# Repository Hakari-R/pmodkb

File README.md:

# pmodkb

---

4x4 MX Keyboard Pmod module

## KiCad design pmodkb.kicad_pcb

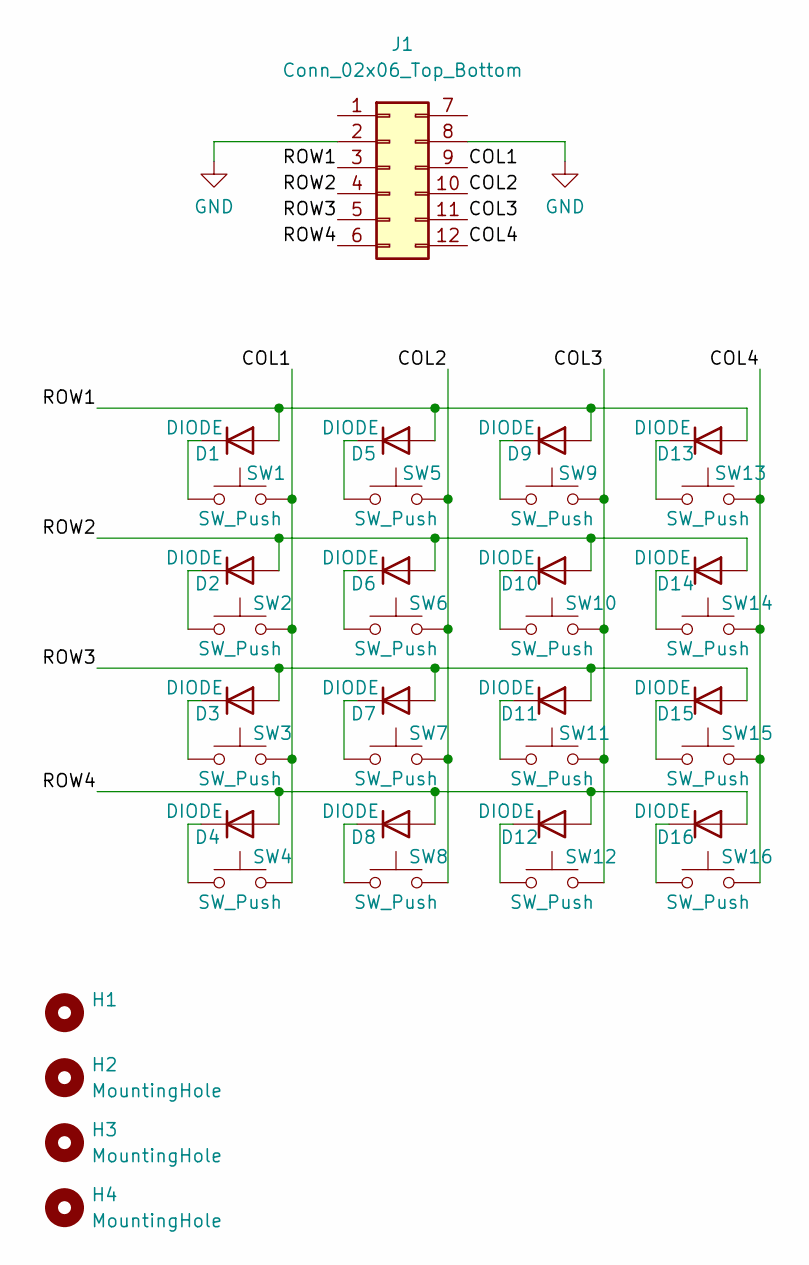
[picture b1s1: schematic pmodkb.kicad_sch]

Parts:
D1, D2, D3, D4, D5, D6, D7, D8, D9, D10, D11, D12, D13, D14, D15, D16: DIODE; D_0805_2012Metric_Pad1.15x1.40mm_HandSolder
H1: (no value)
H2, H3, H4: MountingHole
J1: Conn_02x06_Top_Bottom; PinHeader_2x06_P2.54mm_Horizontal
SW1, SW2, SW3, SW4, SW5, SW6, SW7, SW8, SW9, SW10, SW12, SW13, SW14, SW15, SW16: SW_Push; SW_Cherry_MX_1.00u_PCB
SW11: SW_Push

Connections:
/COL1: J1.9, SW1.2, SW2.2, SW3.2, SW4.2
/COL2: J1.10, SW5.2, SW6.2, SW7.2, SW8.2
/COL3: J1.11, SW9.2, SW10.2, SW11.2, SW12.2
/COL4: J1.12, SW13.2, SW14.2, SW15.2, SW16.2
/ROW1: D1.1 (A), D5.1 (A), D9.1 (A), D13.1 (A), J1.3
/ROW2: D2.1 (A), D6.1 (A), D10.1 (A), D14.1 (A), J1.4
/ROW3: D3.1 (A), D7.1 (A), D11.1 (A), D15.1 (A), J1.5
/ROW4: D4.1 (A), D8.1 (A), D12.1 (A), D16.1 (A), J1.6
GND: J1.2, J1.8
unnamed: D1.2 (K), SW1.1
unnamed: D2.2 (K), SW2.1
unnamed: D3.2 (K), SW3.1
unnamed: D4.2 (K), SW4.1
unnamed: D5.2 (K), SW5.1
unnamed: D6.2 (K), SW6.1
unnamed: D7.2 (K), SW7.1
unnamed: D8.2 (K), SW8.1
unnamed: D9.2 (K), SW9.1
unnamed: D10.2 (K), SW10.1
unnamed: D11.2 (K), SW11.1
unnamed: D12.2 (K), SW12.1
unnamed: D13.2 (K), SW13.1
unnamed: D14.2 (K), SW14.1
unnamed: D15.2 (K), SW15.1
unnamed: D16.2 (K), SW16.1

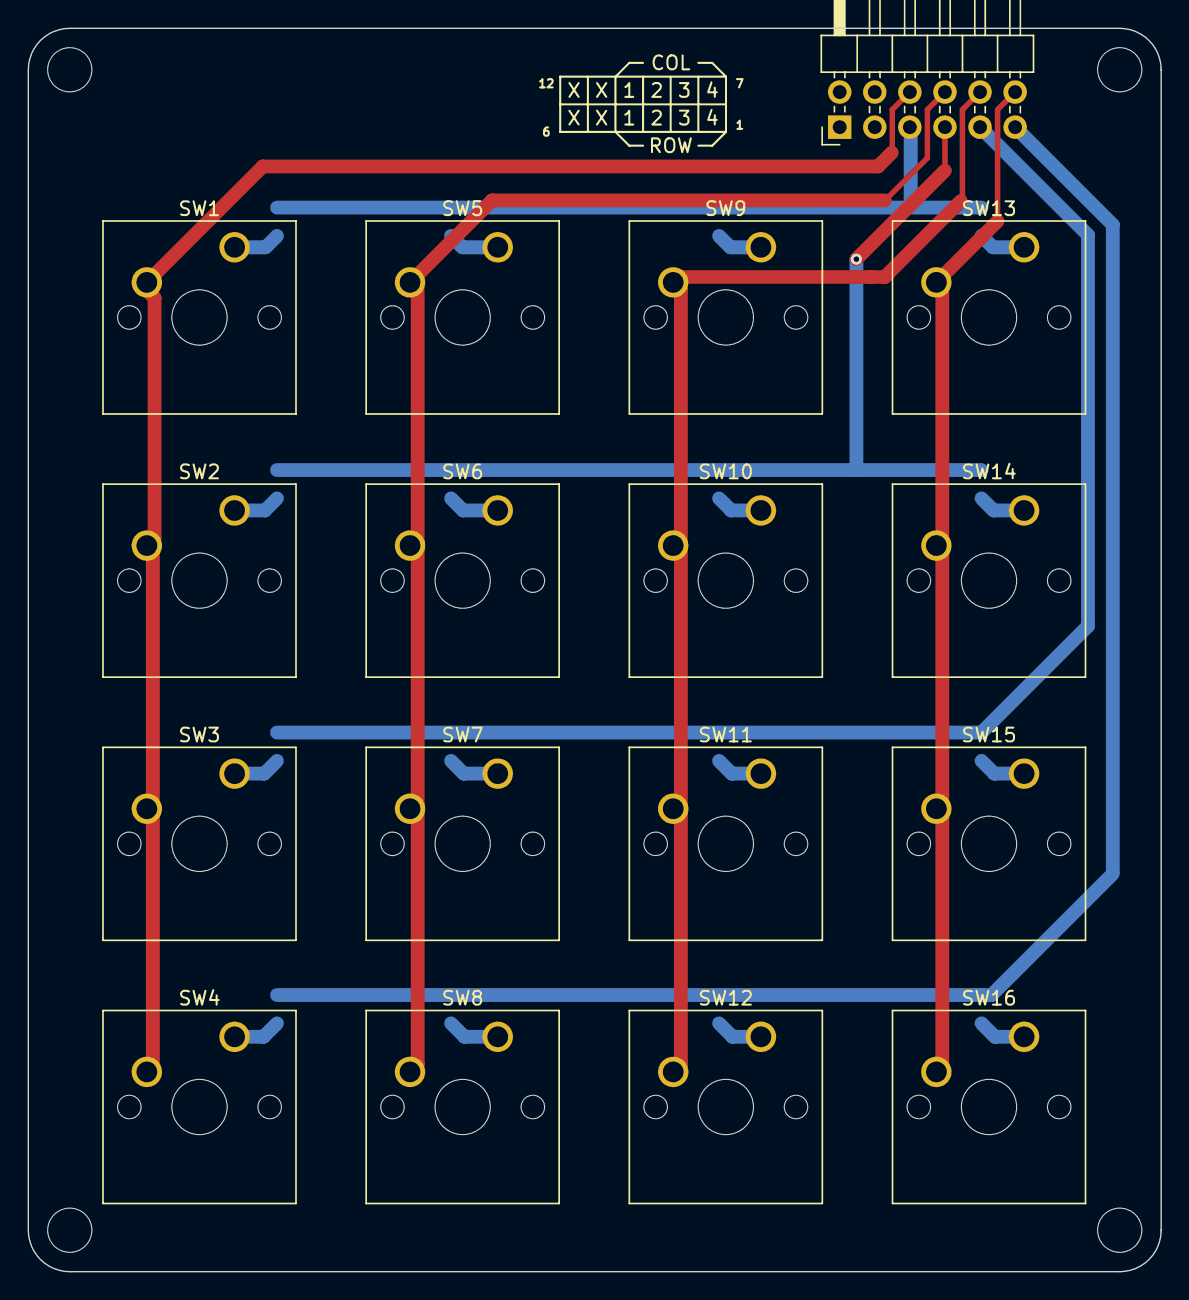
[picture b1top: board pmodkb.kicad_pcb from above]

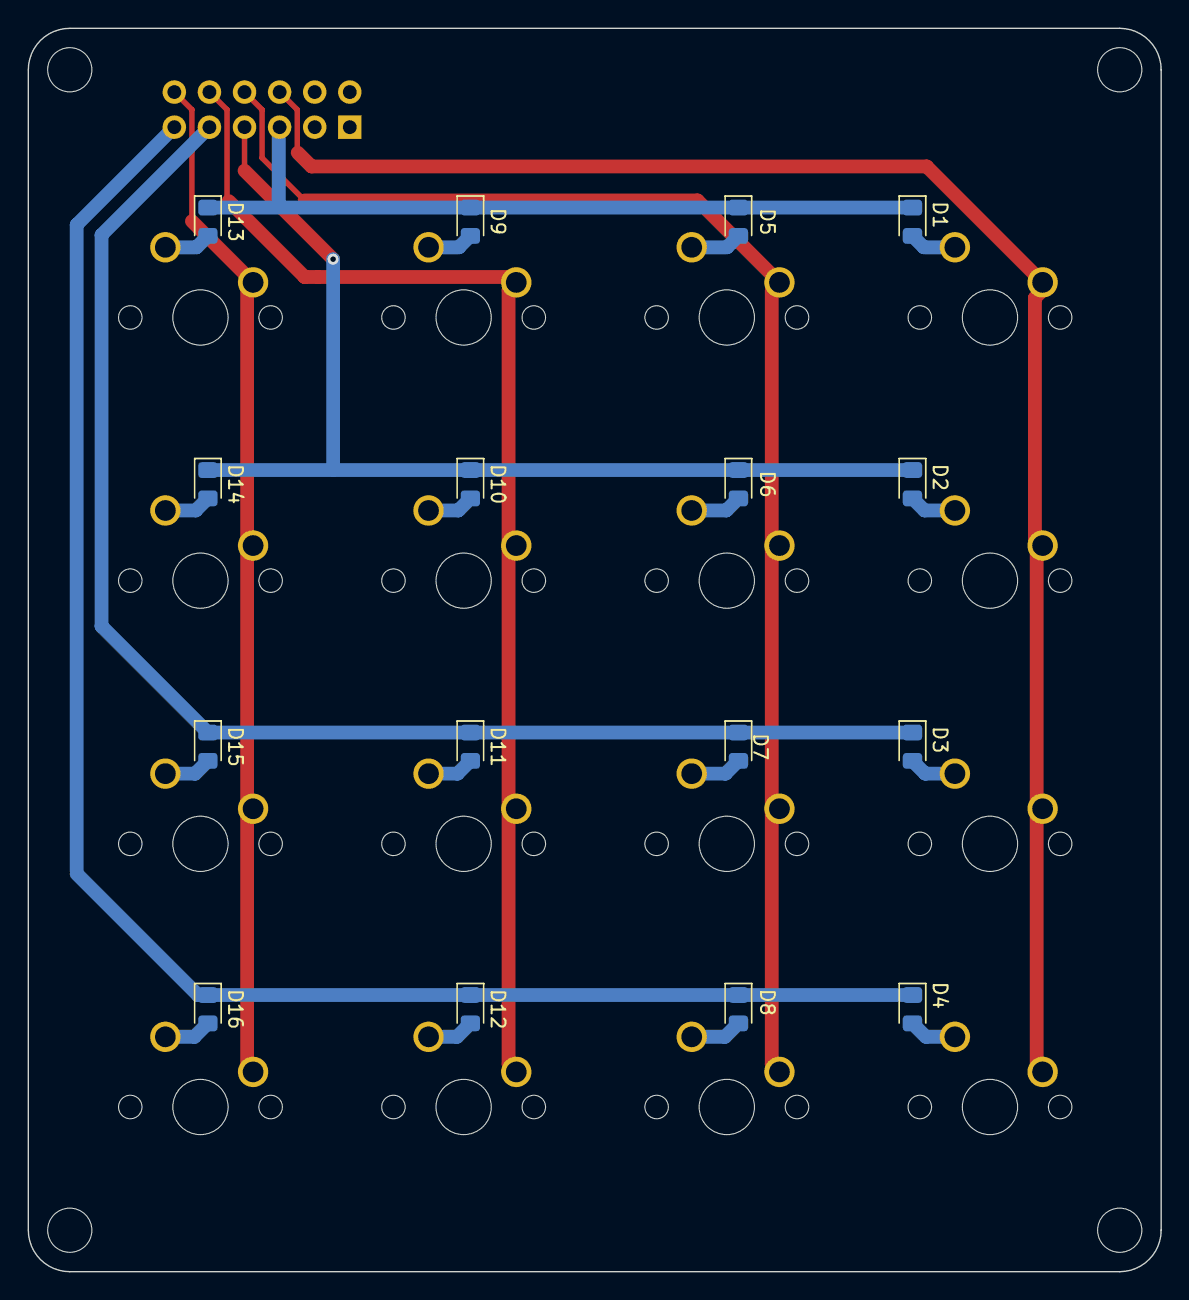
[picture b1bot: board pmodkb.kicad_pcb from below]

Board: 2 copper layers, 82.0 x 90.0 mm, 37 parts (16 on the bottom side), 25 nets.

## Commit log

2022-04-17 init commit
2022-04-17 Add doc
